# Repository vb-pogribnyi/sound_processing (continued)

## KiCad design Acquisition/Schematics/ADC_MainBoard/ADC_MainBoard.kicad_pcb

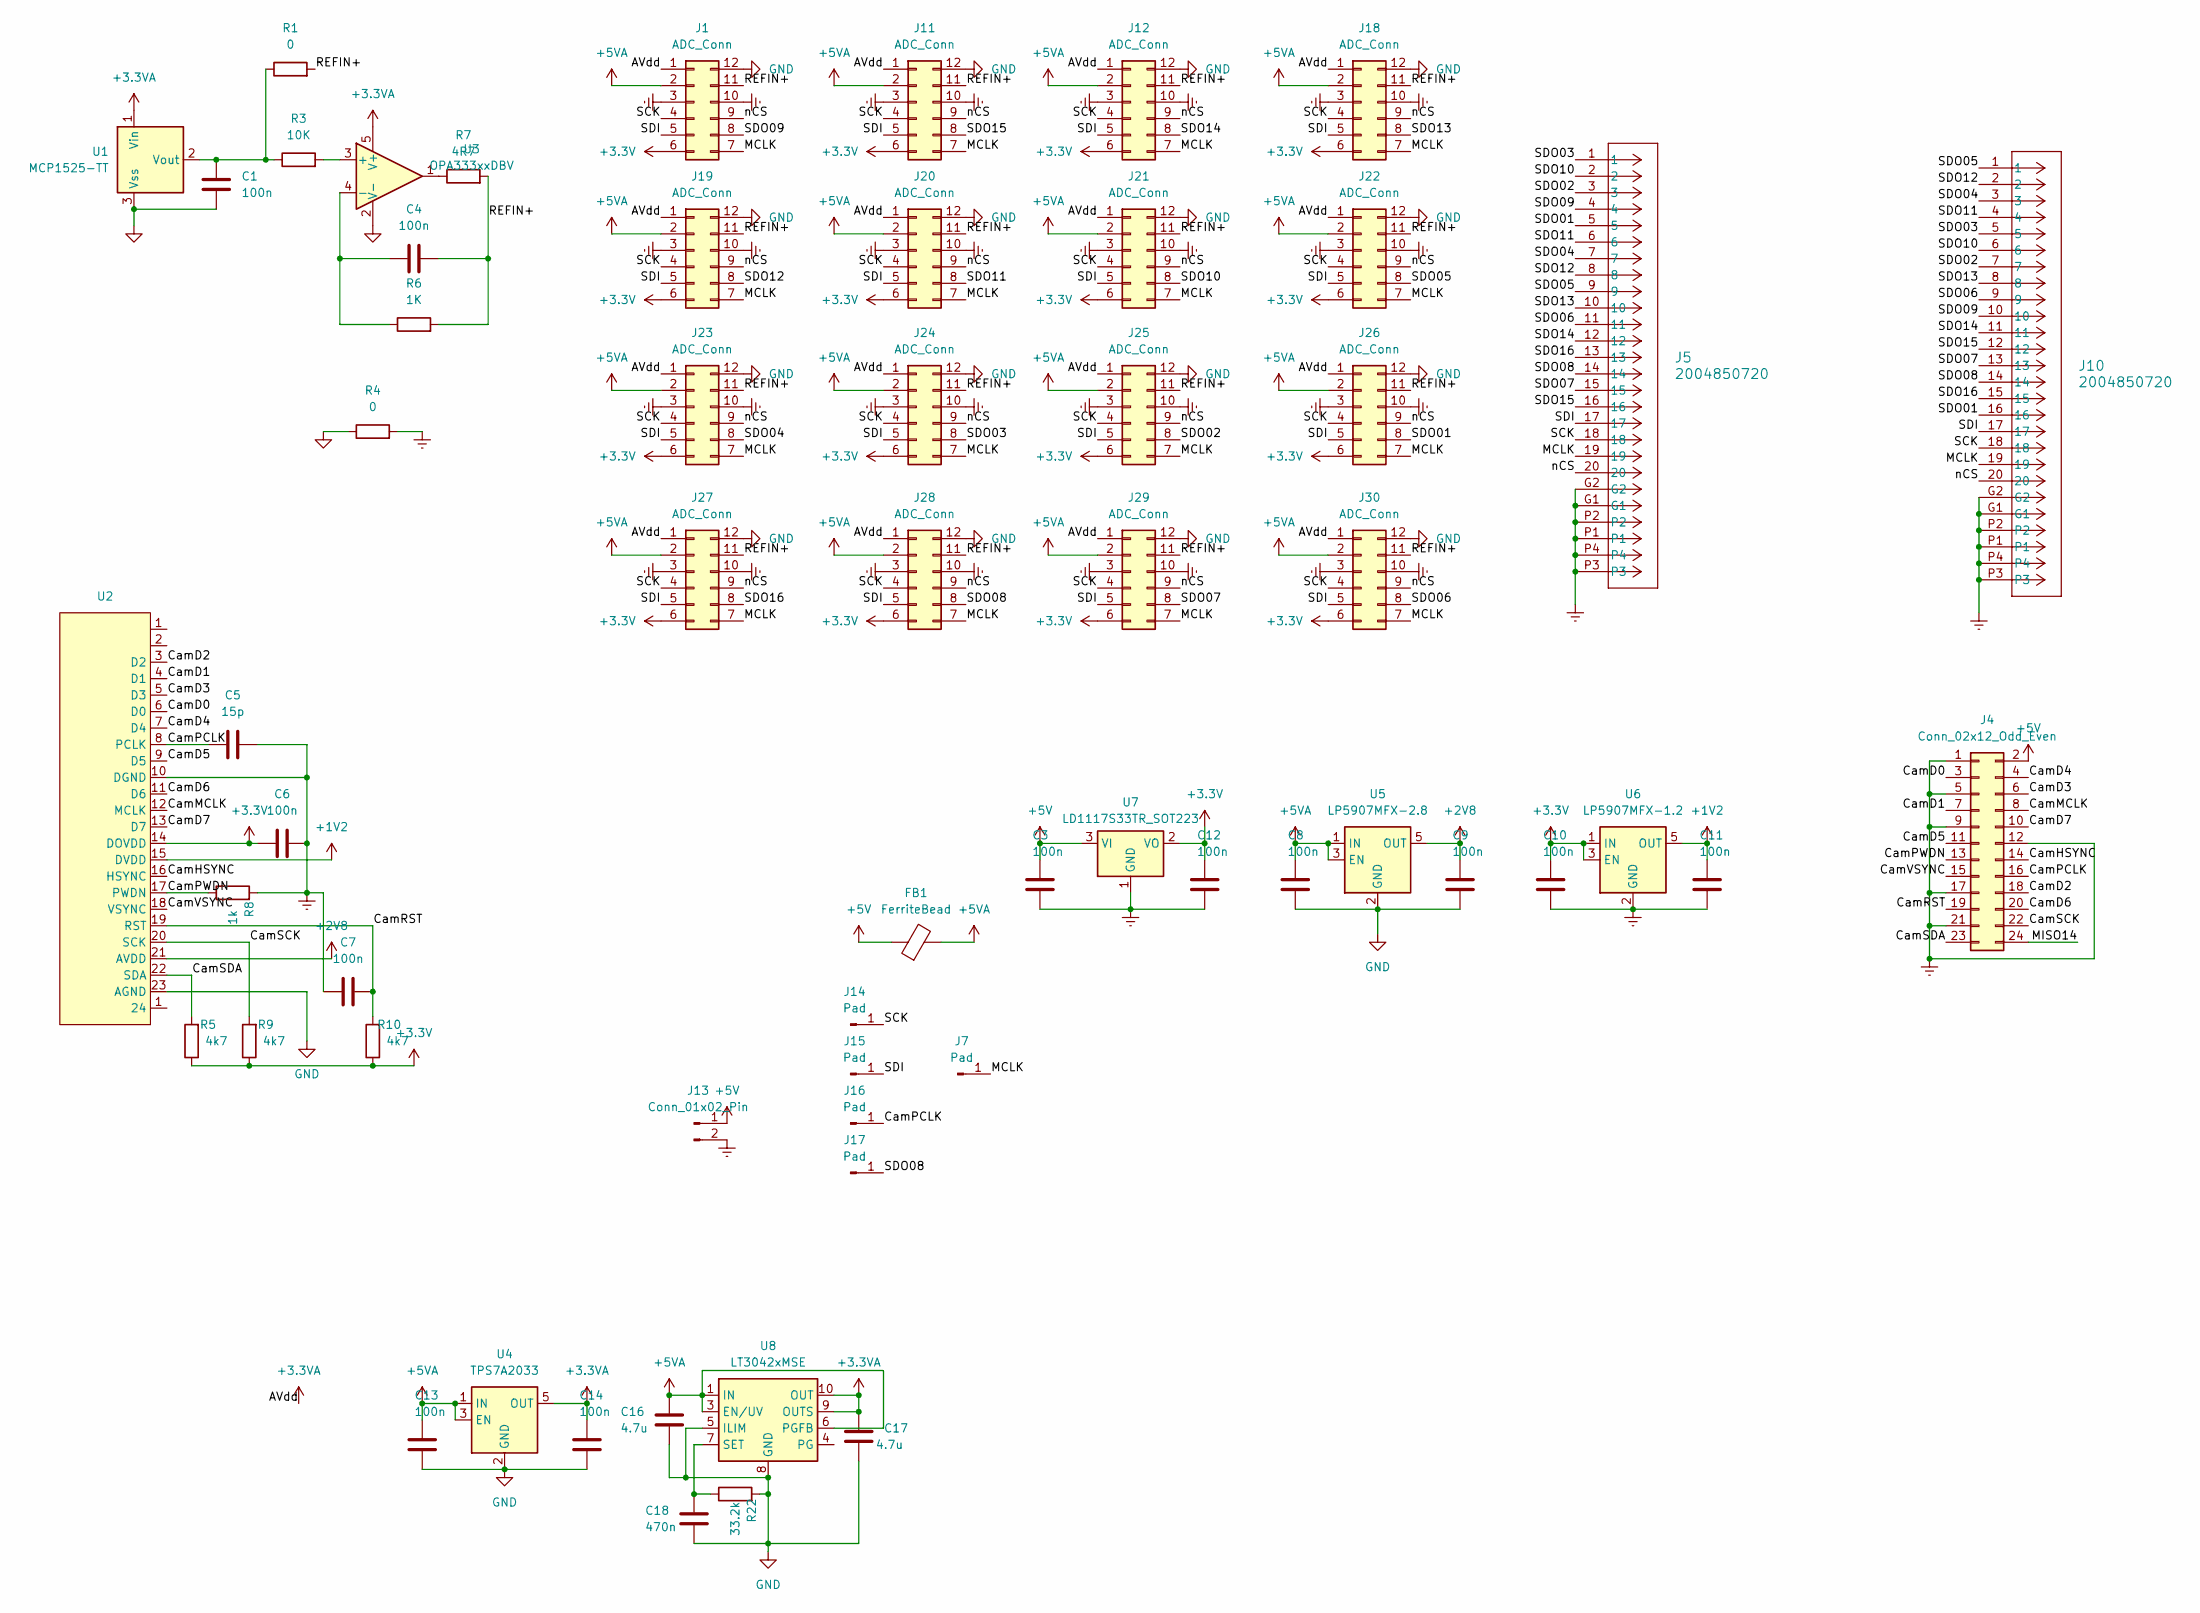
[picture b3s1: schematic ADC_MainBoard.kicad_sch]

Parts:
C1, C3, C4, C8, C9, C10, C11, C12, C13, C14: 100n; C_0603_1608Metric
C5: 15p; R_0603_1608Metric
C6, C7: 100n; R_0603_1608Metric
C16, C17: 4.7u; C_0603_1608Metric
C18: 470n; C_0603_1608Metric
FB1: FerriteBead; CP_Axial_L11.0mm_D6.0mm_P18.00mm_Horizontal
J1, J11, J12, J18, J19, J20, J21, J22, J23, J24, J25, J26, J27, J28, J29, J30: ADC_Conn; KYOCERA AVX Base
J4: Conn_02x12_Odd_Even; PinHeader_2x12_P2.54mm_Vertical
J5, J10: 2004850720; Molex FFC 20pin sideways
J7, J14, J15, J16, J17: Pad
J13: Conn_01x02_Pin; PinHeader_1x02_P2.54mm_Vertical
R1, R4: 0; C_0603_1608Metric
R3: 10K; C_0603_1608Metric
R5, R9, R10: 4k7; R_0603_1608Metric
R6: 1K; C_0603_1608Metric
R7: 4R7; C_0603_1608Metric
R8: 1k; R_0603_1608Metric
R22: 33.2k; R_0603_1608Metric
U1: MCP1525-TT; SOT-23
U2: Hirose_FH12-24S-0.5SH_1x24-1MP_P0.50mm_Horizontal
U3: OPA333xxDBV; SOT-23-5
U4: TPS7A2033; SOT-23-5
U5: LP5907MFX-2.8; SOT-23-5
U6: LP5907MFX-1.2; SOT-23-5
U7: LD1117S33TR_SOT223; SOT-223-3_TabPin2
U8: LT3042xMSE; MSOP-10-1EP_3x3mm_P0.5mm_EP1.68x1.88mm

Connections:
+1V2: C11.1, U2.15 (DVDD), U6.5 (OUT)
+2V8: C9.1, U2.21 (AVDD), U5.5 (OUT)
+3.3V: C6.1, C10.1, C12.1, J1.6, J11.6, J12.6, J18.6, J19.6, J20.6, J21.6, J22.6, J23.6, J24.6, J25.6, J26.6, J27.6, J28.6, J29.6, J30.6, R5.1, R9.1, R10.1, U2.14 (DOVDD), U6.1 (IN), U6.3 (EN), U7.2 (VO)
+3.3VA: C14.1, C17.1, J1.1, J11.1, J12.1, J18.1, J19.1, J20.1, J21.1, J22.1, J23.1, J24.1, J25.1, J26.1, J27.1, J28.1, J29.1, J30.1, U1.1 (Vin), U3.5 (V+), U4.5 (OUT), U8.9 (OUTS), U8.10 (OUT)
+5V: C3.1, FB1.1, J4.2, J13.1, U7.3 (VI)
+5VA: C8.1, C13.1, C16.1, FB1.2, J1.2, J11.2, J12.2, J18.2, J19.2, J20.2, J21.2, J22.2, J23.2, J24.2, J25.2, J26.2, J27.2, J28.2, J29.2, J30.2, U4.1 (IN), U4.3 (EN), U5.1 (IN), U5.3 (EN), U8.1 (IN), U8.2 (IN), U8.3 (EN/UV), U8.6 (PGFB); also elsewhere on the board
/CamD0: J4.3, U2.6 (D0)
/CamD1: J4.7, U2.4 (D1)
/CamD2: J4.18, U2.3 (D2)
/CamD3: J4.6, U2.5 (D3)
/CamD4: J4.4, U2.7 (D4)
/CamD5: J4.11, U2.9 (D5)
/CamD6: J4.20, U2.11 (D6)
/CamD7: J4.10, U2.13 (D7)
/CamHSYNC: J4.14, U2.16 (HSYNC)
/CamMCLK: J4.8, U2.12 (MCLK)
/CamPCLK: C5.1, J4.16, J16.1, U2.8 (PCLK)
/CamPWDN: J4.13, R8.1, U2.17 (PWDN)
/CamRST: C7.1, J4.19, R10.2, U2.19 (RST)
/CamSCK: J4.22, R9.2, U2.20 (SCK)
/CamSDA: J4.23, R5.2, U2.22 (SDA)
/CamVSYNC: J4.15, U2.18 (VSYNC)
/MCLK: J1.7, J5.19, J7.1, J10.19, J11.7, J12.7, J18.7, J19.7, J20.7, J21.7, J22.7, J23.7, J24.7, J25.7, J26.7, J27.7, J28.7, J29.7, J30.7
/MISO14: J4.24
/REFIN+: C4.2, J1.11, J11.11, J12.11, J18.11, J19.11, J20.11, J21.11, J22.11, J23.11, J24.11, J25.11, J26.11, J27.11, J28.11, J29.11, J30.11, R1.2, R6.2, R7.2
/SCK: J1.4, J5.18, J10.18, J11.4, J12.4, J14.1, J18.4, J19.4, J20.4, J21.4, J22.4, J23.4, J24.4, J25.4, J26.4, J27.4, J28.4, J29.4, J30.4
/SDI: J1.5, J5.17, J10.17, J11.5, J12.5, J15.1, J18.5, J19.5, J20.5, J21.5, J22.5, J23.5, J24.5, J25.5, J26.5, J27.5, J28.5, J29.5, J30.5
/SDO01: J5.5, J10.16, J26.8
/SDO02: J5.3, J10.7, J25.8
/SDO03: J5.1, J10.5, J24.8
/SDO04: J5.7, J10.3, J23.8
/SDO05: J5.9, J10.1, J22.8
/SDO06: J5.11, J10.9, J30.8
/SDO07: J5.15, J10.13, J29.8
/SDO08: J5.14, J10.14, J17.1, J28.8
/SDO09: J1.8, J5.4, J10.10
/SDO10: J5.2, J10.6, J21.8
/SDO11: J5.6, J10.4, J20.8
/SDO12: J5.8, J10.2, J19.8
/SDO13: J5.10, J10.8, J18.8
/SDO14: J5.12, J10.11, J12.8
/SDO15: J5.16, J10.12, J11.8
/SDO16: J5.13, J10.15, J27.8
/nCS: J1.9, J5.20, J10.20, J11.9, J12.9, J18.9, J19.9, J20.9, J21.9, J22.9, J23.9, J24.9, J25.9, J26.9, J27.9, J28.9, J29.9, J30.9
Earth: C3.2, C5.2, C6.2, C7.2, C10.2, C11.2, C12.2, J1.3, J1.10, J4.1, J4.5, J4.9, J4.12, J4.17, J4.21, J5.G1, J5.G2, J5.P1, J5.P2, J5.P3, J5.P4, J10.G1, J10.G2, J10.P1, J10.P2, J10.P3, J10.P4, J11.3, J11.10, J12.3, J12.10, J13.2, J18.3, J18.10, J19.3, J19.10, J20.3, J20.10, J21.3, J21.10, J22.3, J22.10, J23.3, J23.10, J24.3, J24.10, J25.3, J25.10, J26.3, J26.10, J27.3, J27.10, J28.3, J28.10, J29.3, J29.10, J30.3, J30.10, R4.2, R8.2, U2.10 (DGND), U6.2 (GND), U7.1 (GND)
GND: C1.2, C8.2, C9.2, C13.2, C14.2, C16.2, C17.2, C18.2, J1.12, J11.12, J12.12, J18.12, J19.12, J20.12, J21.12, J22.12, J23.12, J24.12, J25.12, J26.12, J27.12, J28.12, J29.12, J30.12, R4.1, R22.2, U1.3 (Vss), U2.23 (AGND), U3.2 (V-), U4.2 (GND), U5.2 (GND), U8.5 (ILIM), U8.8 (GND), U8.11 (GND); also elsewhere on the board
unnamed: R7.1, U3.1
unnamed: C1.1, R1.1, R3.1, U1.2 (Vout)
unnamed: R3.2, U3.3 (+)
unnamed: C4.1, R6.1, U3.4 (-)
unnamed: C18.1, R22.1, U8.7 (SET)

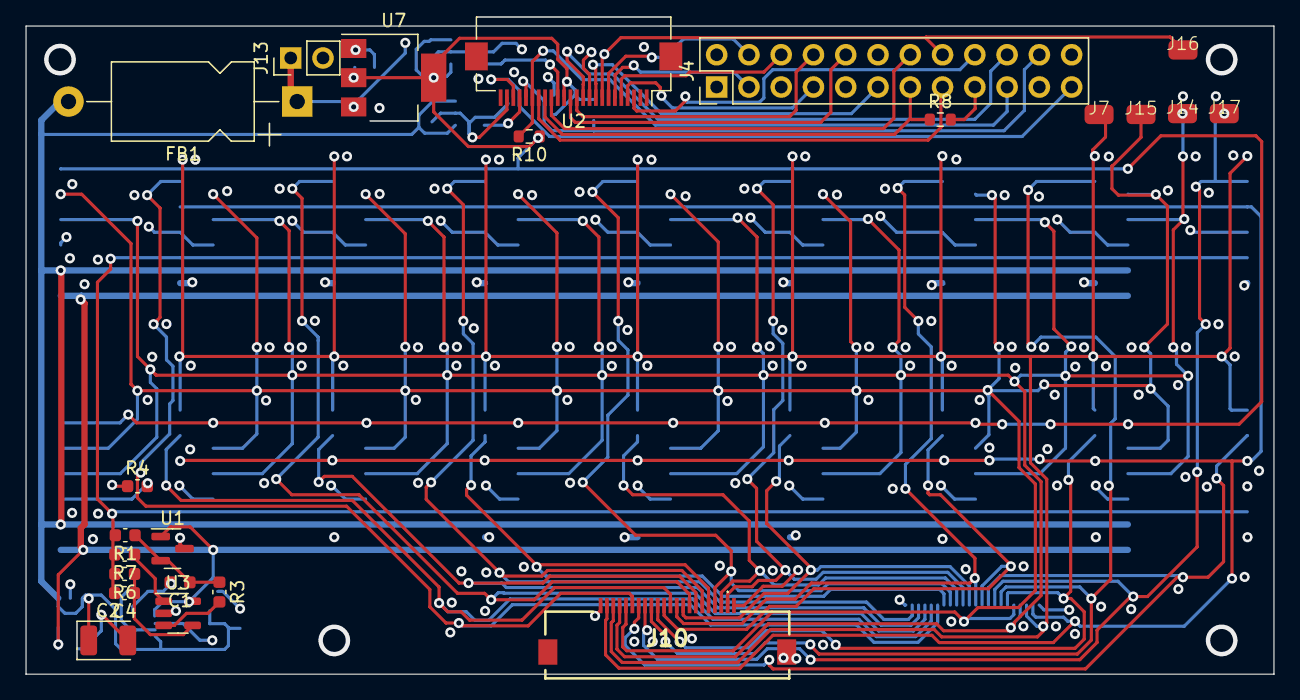
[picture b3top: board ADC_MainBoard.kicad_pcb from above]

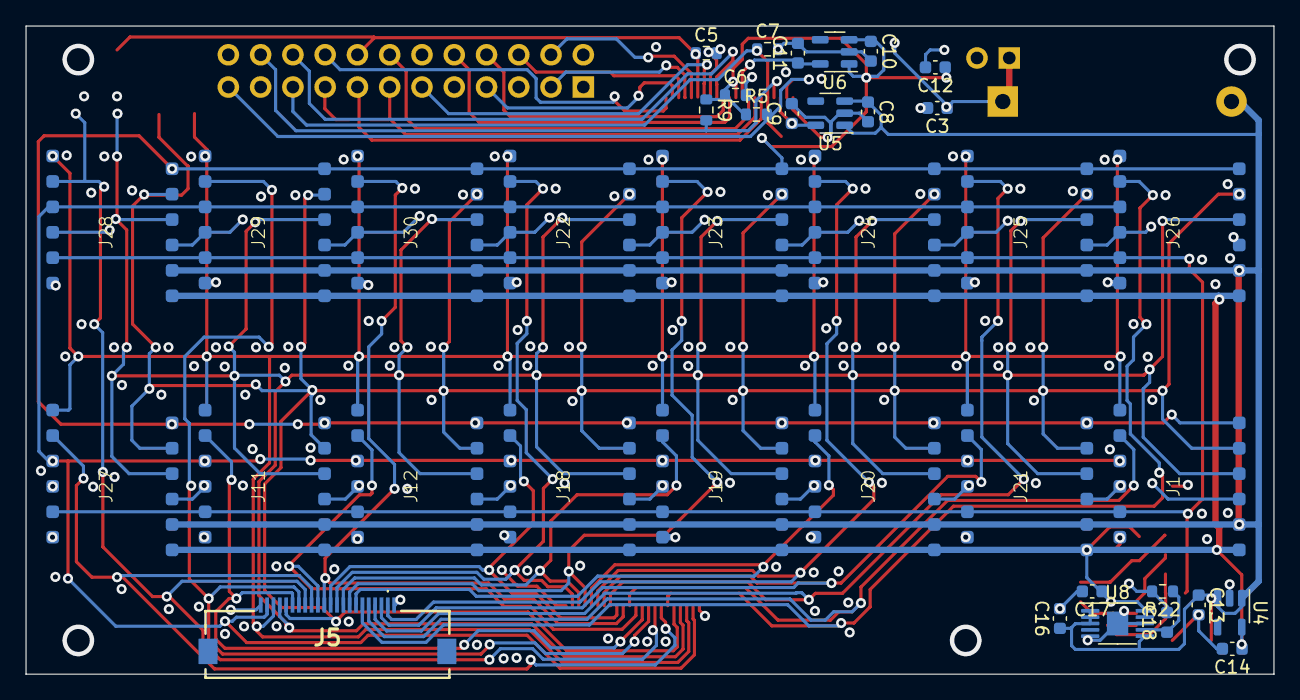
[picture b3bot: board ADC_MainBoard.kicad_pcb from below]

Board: 4 copper layers, 98.2 x 51.0 mm, 61 parts (38 on the bottom side), 50 nets.

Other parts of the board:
C2: 100n; CP_EIA-3528-21_Kemet-B

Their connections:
+5VA: C2.1; also elsewhere on the board
GND: C2.2; also elsewhere on the board

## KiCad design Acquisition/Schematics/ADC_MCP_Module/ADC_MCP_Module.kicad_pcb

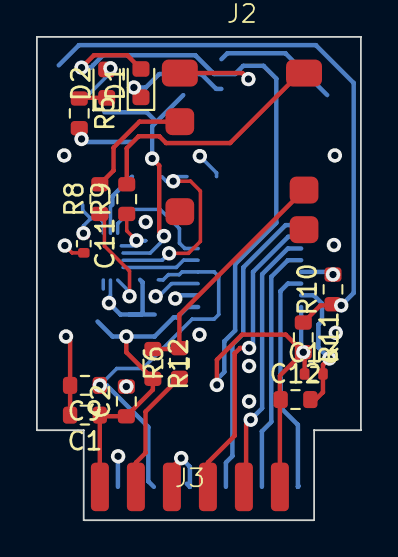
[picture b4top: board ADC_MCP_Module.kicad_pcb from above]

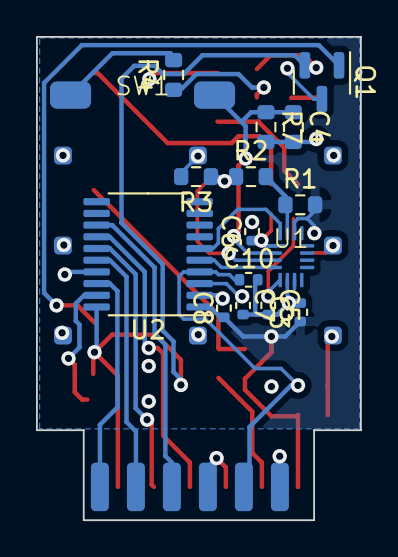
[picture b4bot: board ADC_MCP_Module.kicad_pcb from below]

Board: 4 copper layers, 18.0 x 26.8 mm, 34 parts (17 on the bottom side), 28 nets.

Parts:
C1, C2, C9, C12: 10u; R_0603_1608Metric
C3, C5, C6, C7, C8, C10, C11, C13: 100n; R_0402_1005Metric
C4: 100n; R_0603_1608Metric
D1, D2: LED; LED_0603_1608Metric
J1: Can; Can_15_10
J2: AudioJack4_SwitchTR1; SJ2-35954A
J3: Conn_02x06_Counter_Clockwise; KYOCERA AVX
Q1: IRLML9301; SOT-23
R1, R2, R3: 1k; R_0603_1608Metric
R4, R5, R11: 470R; R_0603_1608Metric
R6, R12: 0; R_0603_1608Metric
R7: 10k; R_0603_1608Metric
R8, R9: 100; R_0603_1608Metric
R10: 10; R_0603_1608Metric
SW1: SW_DIP_x01; BTN (PTS636SM25SMTR)
U1: UQFN-16
U2: TSSOP-20_4.4x6.5mm_P0.65mm

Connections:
+3.3V: C12.1, C13.1, D1.2 (A), J3.6, Q1.2 (S), R11.2, U2.20 (DVdd)
+5VA: J3.2, R6.1
/AVdd: C1.1, C2.1, C3.1, C8.1, C11.1, J3.1, R1.2, R12.2, U1.14 (Vcc), U2.1 (Avdd)
/DIV1: R2.1, R3.1, U1.3 (In2_1)
/DIV2: R1.1, R2.2, U1.15 (In1_1)
/IN_Ctrl: C4.1, R7.1, SW1.2, U1.2 (Ctrl12)
/MCLK: J3.7, U2.18 (MCLK)
/MIC_1: C6.1, R9.1, U1.1 (In1_0)
/MIC_2: C5.1, R8.1, U1.5 (In2_0)
/OUT1: U1.4 (Out2), U2.5 (CH0)
/OUT2: U1.16 (Out1), U2.6 (CH1)
/Out: J3.8, U2.16 (SDO)
/REFIN+: C9.1, C10.1, J3.11, U2.4 (REFIN+/OUT)
/SCK: J3.4, U2.14 (SCK)
/SDI: J3.5, U2.15 (SDI)
/nCS: J3.9, U2.13 (nCS)
/nIRQ: Q1.1 (G), R10.1, R11.1
Earth: C4.2, C12.2, C13.2, J3.3, J3.10, R5.2, R7.2, U2.19 (Dgnd)
GND: C1.2, C2.2, C3.2, C5.2, C6.2, C7.2, C8.2, C9.2, C10.2, C11.2, J1.1, J2.S, J3.12, R3.2, U1.6 (GND), U2.2 (Agnd)
unnamed: D1.1 (K), R4.1
unnamed: D2.2 (A), Q1.3 (D)
unnamed: D2.1 (K), R5.1
unnamed: J2.R1, R8.2
unnamed: J2.R2, R9.2
unnamed: J2.T, R6.2, R12.1
unnamed: R4.2, SW1.1
unnamed: C7.1, U2.3 (REFIN-)
unnamed: R10.2, U2.17 (nIRQ/MDAT)

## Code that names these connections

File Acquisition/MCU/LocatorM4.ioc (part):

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Mcu.Name=STM32F407V(E-G)Tx
Mcu.Package=LQFP100
Mcu.UserName=STM32F407VETx
PA10.GPIOParameters=GPIO_PuPd,GPIO_Label
PA10.GPIO_Label=FPGA_Status
PA10.GPIO_PuPd=GPIO_PULLDOWN
PA10.Signal=GPIO_Input
PA13.Mode=Serial_Wire
PA13.Signal=SYS_JTMS-SWDIO
PA14.Mode=Serial_Wire
PA14.Signal=SYS_JTCK-SWCLK
PA3.Mode=Device_HS
PA3.Signal=USB_OTG_HS_ULPI_D0
PA5.Mode=Device_HS
PA5.Signal=USB_OTG_HS_ULPI_CK
PA7.Mode=Full_Duplex_Master
PA7.Signal=SPI1_MOSI
PA9.GPIOParameters=GPIO_PuPd,GPIO_Label
PA9.GPIO_Label=FPGA_Done
PA9.GPIO_PuPd=GPIO_PULLDOWN
PA9.Signal=GPIO_Input
PB0.Mode=Device_HS
PB0.Signal=USB_OTG_HS_ULPI_D1
PB1.Mode=Device_HS
PB1.Signal=USB_OTG_HS_ULPI_D2
PB10.Mode=Device_HS
PB10.Signal=USB_OTG_HS_ULPI_D3
PB11.Mode=Device_HS
PB11.Signal=USB_OTG_HS_ULPI_D4
PB12.Mode=Device_HS
PB12.Signal=USB_OTG_HS_ULPI_D5
PB13.Mode=Device_HS
PB13.Signal=USB_OTG_HS_ULPI_D6
PB3.Mode=Full_Duplex_Master
PB3.Signal=SPI1_SCK
PB4.Mode=Full_Duplex_Master
PB4.Signal=SPI1_MISO
PB5.Mode=Device_HS
PB5.Signal=USB_OTG_HS_ULPI_D7
PB7.Signal=FSMC_NL
PB9.GPIOParameters=GPIO_Label
PB9.GPIO_Label=LED_R
PB9.Signal=GPIO_Output
PC0.Mode=Device_HS
PC0.Signal=USB_OTG_HS_ULPI_STP
PC1.GPIOParameters=GPIO_Label
PC1.GPIO_Label=USB_RST
PC1.Signal=GPIO_Output
PC10.Mode=Full_Duplex_Master
PC10.Signal=SPI3_SCK
PC11.Mode=Full_Duplex_Master
PC11.Signal=SPI3_MISO
PC12.Mode=Full_Duplex_Master
PC12.Signal=SPI3_MOSI
PC2.Mode=Device_HS
PC2.Signal=USB_OTG_HS_ULPI_DIR
PC3.Mode=Device_HS
PC3.Signal=USB_OTG_HS_ULPI_NXT
PD0.Mode=8b-da1
PD0.Signal=FSMC_DA2
PD1.Mode=8b-da1
PD1.Signal=FSMC_DA3
PD14.Mode=8b-da1
PD14.Signal=FSMC_DA0
PD15.Mode=8b-da1
PD15.Signal=FSMC_DA1
PD3.Mode=BurstRead1
PD3.Signal=FSMC_CLK
PD4.Mode=MuxedPsram1
PD4.Signal=FSMC_NOE
PD5.Mode=MuxedPsram1
PD5.Signal=FSMC_NWE
PD6.Mode=AsynchronousSynchronousWait1
PD6.Signal=FSMC_NWAIT
PD7.Mode=NorPsramChipSelect1_1
PD7.Signal=FSMC_NE1
PE0.GPIOParameters=GPIO_Label
PE0.GPIO_Label=LED_G
PE0.Signal=GPIO_Output
PE1.GPIOParameters=GPIO_Label
PE1.GPIO_Label=LED
PE1.Signal=GPIO_Output
PE10.Mode=8b-da1
PE10.Signal=FSMC_DA7
PE2.GPIOParameters=GPIO_Label
PE2.GPIO_Label=LED2
PE2.Signal=GPIO_Output
PE7.Mode=8b-da1
PE7.Signal=FSMC_DA4
PE8.Mode=8b-da1
PE8.Signal=FSMC_DA5
PE9.Mode=8b-da1
PE9.Signal=FSMC_DA6
PH0-OSC_IN.Mode=HSE-External-Oscillator
PH0-OSC_IN.Signal=RCC_OSC_IN
PH1-OSC_OUT.Mode=HSE-External-Oscillator
PH1-OSC_OUT.Signal=RCC_OSC_OUT
RCC.HSE_VALUE=25000000
RCC.SYSCLKFreq_VALUE=168000000
RCC.SYSCLKSource=RCC_SYSCLKSOURCE_PLLCLK
board=custom

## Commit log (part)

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2026-04-04 Compiles on my machine
2026-04-04 Added (stolen) kwave python
2026-04-05 Added circular signal generation
2026-04-05 Added support for periodic input pressure
2026-04-07 Seems working with reduced file size.
2026-04-08 Added sound generation
2026-04-10 Added sampling period - seems working
2026-04-11 Runs whole input file at once
2026-04-11 Stopping and resuming seems stable.
2026-04-13 Optimized inputs loading
2026-04-13 Removed OMP version of kwave
2026-04-13 Using profile generated map as a mask.
2026-04-14 Added results for shaped-sine signal.
2026-04-15 Added tmpfs, re-generating input files.
2026-04-17 Added heterogenous density and sound speed
2026-04-18 Added sound speed/density noise
2026-04-18 Experimenting - sketched basic structure.
2026-04-19 Runs experiment in own folder with values read from the config.
2026-04-19 Added result exporting
2026-04-19 Added mesh resampler
2026-04-20 Fixed source resampling.
2026-04-21 Integrated mesh reader & basic exporter
2026-04-23 Exported debug looks correct
2026-04-23 Adapted for scaling
2026-04-23 Populated the exported data with values from simulation.
2026-04-24 Saves data in pickle format
2026-04-24 Added option for stationary mesh
2026-04-25 Added separate process for GIFs generation.
2026-04-25 Added asynchronous sources loading
2026-04-25 Extended logger, added separate experiments dir
2026-04-26 Added slices export, fixed spheres noise
2026-04-27 MeshReader timing fix
2026-04-27 Added gradual exports, fixed glitched shifts.
2026-04-28 Added bulk profile generation
2026-04-30 Fixed export
2026-05-02 Moved into subdirectory
2026-05-03 Fixed filepaths
2026-05-03 Restarting fix
2026-05-03 Added processing scripts
2026-05-04 Removed sync between waveforms (itimestamps not precise enough)
2026-05-05 Little bit organization
2026-05-05 TAME - as is
2026-05-05 Modified generator for TAME dataloader
2026-05-06 Cross3D - as is
2026-05-07 Fixed finalization & resuming process
2026-05-07 Seems to be training
2026-05-08 Conformer - as is
2026-05-08 Adapted ResNet backbone
2026-05-08 Moving directories...
2026-05-09 Draft of a universal training script
2026-05-09 Conformer training on MMAUD dataset
2026-05-09 Cross3D working with unified train script
2026-05-10 Added script converting from KWave export to MMAUD format.
2026-05-13 Added exporting microphones positions for mmaud
2026-05-16 Added full MMAUD export script
2026-05-17 Added TAME into the train pipeline
2026-05-19 Added cartesian coordinates of the source
2026-05-19 MLflow integration
2026-05-19 Logging visualizations into mlflow
2026-05-20 Adapted Cross3D for work with updated SRP and spectrogram
2026-05-20 Adapted all models for all preprocessing methods
2026-05-21 Added visualizations for predictions
2026-05-22 Added train predictions visualization
2026-05-22 Added option to try all permutations in val dataloader
2026-05-23 Updated profile generation and larger experiment config
2026-05-23 Documentation updates
2026-05-26 Added captured dataset conversion
2026-05-27 Added optimization note
2026-05-27 Added resampling and saving sample rate & length
2026-05-28 Added ACS augmentation - draft
2026-06-02 Current FPGA configuration code
2026-06-04 FPGA MCP3461 - in progress
2026-06-08 ADC reader - SPI seems adequate.
2026-06-08 Fixed RX
2026-06-09 Added submodule for reading single ADC.
2026-06-09 Fixed commands and outputting state.
2026-06-10 Synthesizes but does not route MOSOs
2026-06-12 ADC - Signs of life
2026-06-13 Works, but noisy and seems glitchy on Android.
2026-06-13 Added ADC module schematic
2026-06-16 Added first version of main board
2026-06-17 PSRAM draft - claude
2026-06-17 ADC board prototype - ORDER
2026-06-19 FSMC - Implements
2026-06-20 Works with STM32
2026-06-23 progress...
2026-06-23 Claude claims self-check is valid
2026-06-23 Claude claims PSRAM.v is ready
2026-06-25 Seems ready for synthesis
2026-06-25 Synthesis works, psram passes self-check.
2026-06-25 Reads back first 9 values
2026-06-25 Seems working with write-readback from STM32
2026-06-27 ADC capture via FSMC working
2026-06-27 Camera - in progress.
2026-06-27 Camera seems working correctly.
2026-06-30 ADC gain selector
2026-06-30 FPGA board schematic
